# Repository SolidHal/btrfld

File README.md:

# btrfld and btrfld_ulp

Pronounced "butter-fold"

A foldable, portable sibling of the btrfly keyboard https://github.com/SolidHal/btrfly-keyboard

and a variant, the btrfld ulp (ultra low profile)

More images available in "FinishedPictures" folder

the btrfld folding and unfolding

the btrfld ultra low profile (ulp) from above

the handwired and pcb version of the choc btrfld

the btrfld ultra low profile (ulp) from above, folded

the handwired and pcb version of the choc btrfld, folded up

the btrfld ultra low profile (ulp) next to the btrfld pcb aka choc (its 7mm thinner!)

the handwired and pcb version of the choc btrfld with its sibling, the btrfly

## Features
- 5 key dactyl-manuform-mini thumb cluster
- flat, tented qwerty keys
- 6 extra mappable keys
- bluetooth (optional)
- folds flat for portability

- btrfld
  - choc switches
  - ~22.5 mm thick
  
- btrfld ulp
  - cherry mx ulp switches
  - ~15.5 mm thick

- 15.5mm thick (btrfld ulp)
- 22.5mm thick (btrfld)

## PCBs

- located in `btrfld_pcb`
- the hand and thumb pcbs are mirrored so they can be used for either hand
- 2 x btrfld_pcb
- 1 x btrfld_pcb_center
- 2 x btrfld_pcb_thumb

## Parts:

- PCBs

- USB C breakout basic breakout board
  - Used this one https://www.amazon.com/Type-C-Breakout-Serial-Connector-Converter/dp/B09KC1SMGD/
  - wiring the usb:
  ```
  For most usages, you can just connect VBUS to your 5V input, GND to ground, and D+ and D- as you expect. You can monitor the CC and SBU pins to determine cable polarity, or send side-band data. Or leave them disconnected
  ```

- A USB 2.0 USB C cable to cut up
  - USB C to Micro usb can be gotten pretty cheap

- 46 choc v1 keyswitches, keycaps OR 46 Cherry MX ULP switches
  - https://github.com/pashutk/Cherry_MX_ULP has information on finding ulp switches
  - if you choose to use ULP switches, you will need to order the solder paste stencils as well as the pcbs and get a hotplate so you can solder them
  - There aren't amazing sources of ULP key caps at this point. The best option i found was to print some. The stls can be found in `ulp_keycap` and `ulp_keycap_homenub` directories. You need a reasonably high resolution SLA printer to get functional keycaps, FDM won't work. 

- 1N4148W SOD-323F diodes
  - Tips for soldering these can be found in the assembly notes section below

- 3mm diameter steel rod
  - 2x 70.5mm
  - 2x 64.7mm
  - 2x 22.7 mm
  - 4x 14.2

- 1.27mm flat ribbon cable
  - 2 x 9 wire cables: 13 cm
  - 2 x 6 wire cables: 9.6 cm

- 1x nicenano OR bluemicro840
  - if you don't want bluetooth, you can just use a promicro instead

- 3d printed pieces, located in the STLs folder
  - 1 copy of everything besides test_fit-UnderbodyWireGuides.stl, which we need 4 of

## Print Settings:
```
Supports on buildplate
Detect Bridging
100% infill
0.20mm
PLA/PETG
```

## Assembly Tips
this process is much less tedious than hand wiring. But its still annoying in places since we are trying to keep things thin.

- btrfld (non-ulp)
    - solder the parallel wires to the hands/thumb clusters *before* placing the boards in the frame and soldering switches
    - trim the stabs on the hinge side keys of the left/right hand bodies (switches for Q,A,Z, P, ;, / keys)

- btrfld ulp
    - use your hotplate to solder the switches first, then the diodes, then the parallel wires. you can then install the pcbs into the 3d printed frames
    - you might need to use something to support balance some switches while solder, since some are only partially supported by the PCB
    - the tolerance between the keycaps and the frames is quite tight. do some testing (and likely sanding) before fully assembling to ensure nothing sticks
    
- stripping ribbon cable:
  - take an xacto knife ~3mm from the end of the cable and cut a slit until you see wire, then use your fingernail to peel the cut off section away from the rest of the cable
- use cut off diode/resistor legs to connect the controller to the center pcb
- the pcbs are designed to hold the diodes "upside down" to keep things as thin as possible. Soldering these is a little hard since they like to stick to the soldering iron.
  - get some fine point electronics tweezers
  - put a very very small amount of solder on one of the diode pads
  - place the diode, the "legs" should keep the diode from completely falling into the hole
  - hold the diode down with the tweezers, and use your iron to reflow the solder. This should hold the diode down enough for you to solder the other diode leg.
  - finally, add some more solder to the first pad
- The UnderbodyWireGuides get super glued into the holes of the pcb. See pictures of the hand underside for details.
- Once you have tested the board, use some superglue to reinforce the ribbon cable solder joints

- Reference the images in the "BuildPictures/PCB" folder

## Flash ZMK Firmware

Prebuilt firmware available in the `Firmware` directory
Bridge ground + reset twice quickly to put the bluemicro840 into flashing mode
Or press the "bootloader" key on the keyboard if you have already flashed the firmware before
then copy the firmware onto the keyboard
```
cp build/zephyr/zmk.uf2 /media/<user>/NRF52BOOT/CURRENT.UF2
```

## Build ZMK Firmware

### Github Actions Build

_This is broken until https://github.com/zmkfirmware/zmk/pull/1499 merges, do a local build instead_
fork this repo, modify the files to your hearts content
the github actions workflow will then build it for you
https://github.com/SolidHal/zmk-config-btrfld

### Local build

Grab my fork of the zmk firmware
```
git clone https://github.com/SolidHal/zmk.git
```

follow https://zmk.dev/docs/development/setup
then
```
cd zmk
cd app
west build -b bluemicro840_v1 -- -DSHIELD=btrfld
```

make pristine
```
west build -p -b bluemicro840_v1 -- -DSHIELD=btrfld
```

## Future development
- Attach trackpoint/ball or touchpad somewhere?
- latch to keep folded?
- latches to retain body/thumb extensions in base?

## Modifying
Edit `test_fit.FCStd` using FreeCad, I used version `0.19-24366`
I am by no means a FreeCad expert, so I'm sure it is built suboptimally.
The pcbs were created in kicad

## Hand Wiring Assembly Tips

### Don't hand wire this thing unless you have lots and lots of time to waste. Use the PCBs instead.

- Wiring the underside of the right/left body halves is very tedious
  - Make sure everything stays as flat as possible

- Reference the images in "BuildPictures" and "FinishedPictures" for hints on how to layout the wires

- Reference WiringGuide.png to see see the row/colomn layout

- Must trim a very very slight amount off of the center pin on keyswitches over the body/thumbcluster rod
  - switch above this must be rotated to give clearance for the rod locker

- Body/ThumbCluster Pivot Rob
  - BodyThumbRod Cap gets glued on body end of rod
  - thumb cluster end of rod gets glued in place

- Area around the body/baseplate hinge needs clearence, so keep all wires to the other side of the keyswitch

- Reference the images in the "BuildPictures" folder

### Hand Wiring Wire lengths:

#### Body -> Baseplate
9 wires
420mm

#### Thumb -> Baseplate
6 wires
240mm
70mm threaded through on the thumb side

## References

Animation:
BaseBodyAngle goes from 0 -> 32

firmware:
https://zmk.dev/docs/development/new-shield
https://zmk.dev/docs/development/setup/
https://zmk.dev/docs/troubleshooting
https://github.com/SolidHal/zmk

Friction fit redesign notes:
https://markforged.com/resources/blog/joinery-onyx
https://www.hubs.com/knowledge-base/how-design-snap-fit-joints-3d-printing/

Cherry MX ULP references:
https://github.com/pashutk/Cherry_MX_ULP

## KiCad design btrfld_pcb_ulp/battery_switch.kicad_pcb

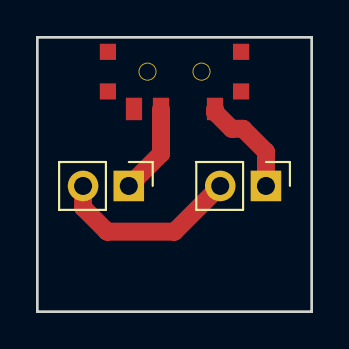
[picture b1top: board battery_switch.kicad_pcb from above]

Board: 2 copper layers, 15.2 x 15.2 mm, 3 parts (0 on the bottom side), 3 nets.

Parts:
J1, J2: Conn_01x02; Pin_Header_Straight_1x02_Pitch2.54mm
SW1: SW_SPDT; SPDT_C128955

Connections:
unnamed: J1.1, SW1.2
unnamed: J1.2, J2.2
unnamed: J2.1, SW1.1

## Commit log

2021-12-21 initial test fit files
2021-12-21 add thumb portion to fit test
2021-12-24 change thumb cluster angle to 40 deg
2021-12-24 add stl, sliced files
2021-12-27 bodies with pivot points
2021-12-30 begin assembly
2021-12-30 aligned LCSes
2021-12-30 map out baseplate
2021-12-31 adjusted pivots to fix 3mm rods
2021-12-31 correct baseplace length
2022-01-01 add readme with partslist
2022-01-01 adjust hole size, baseplate size from 2nd draft print
2022-01-01 add demo animation
2022-01-01 fix demo video, seems freecad outputs weirdness
2022-01-01 need to figure out thumb baseplate attachement
2022-01-01 try smaller support for thumbs
2022-01-01 make thumb right its own piece
    it needs to be unique from thumb left
2022-01-04 cleanup thumb sketch
    - begin work on thumb extension
2022-01-04 rough shape of thumb extension figured out
2022-01-04 get better idea of the thumb extension
2022-01-04 magnetic connector checkpoint
    making the extension wide enough to fit the magnetic connector
    requires either
    1) putting a hole in the baseplate
    2) making the space between the baseplate and the bode/thumb larger
    (2) is bad because we don't want to increase the thickness of the entire
    keyboard
2022-01-05 mapped out one side of extension slot
2022-01-05 bottom, top sketch of baseplate hole for thumb extension
2022-01-06 setup right extension
    cleanup repo
2022-01-06 baseplate thumb extension holes slightly larger
    added route for baseplate body support hinge
2022-01-07 increase thumb extension gap
2022-01-07 support placed
2022-01-07 reduce clearance on thumb extension pivot
2022-01-07 checkpoint
2022-01-07 create sketchs for top and bottom of extension slot
2022-01-07 finally got the subtractive loft to work
2022-01-08 after a bunch of trig, top of slight is aligned
2022-01-08 make body/baseplate hinge 1.7r
2022-01-08 make long holes teardrop shaped
2022-01-09 make baseplate body support hinge larger
2022-01-09 correct baseplate body angle
2022-01-09 add print time reducer for body
2022-01-09 lengthen thumb extension
2022-01-09 add thumb extension stopper
2022-01-09 reworking baseplate/body support, checkpoint
2022-01-11 add symmetric body/baseplate support
2022-01-11 completed baseplate body support
2022-01-11 correct body support spacing
2022-01-11 move supports in a bit to make slicer happy
2022-01-12 remove external references on body pieces
2022-01-12 move thumb clusters inward
2022-01-12 adjust thumb cluster angle
2022-01-13 clean up attactment points
2022-01-13 move thumb cluter hinge up
2022-01-13 Revert "move thumb cluter hinge up"
    This reverts commit d1044715d7c4dff2feddb821aab7251de043a833.
2022-01-13 fixup thumb extension baseplate slots
2022-01-13 change angle of thumb cluster to body
2022-01-13 fixup thumb extension and thumb placement to fit angle change
2022-01-13 correct thumb cluster body linear extension
2022-01-13 correct thumb extension baseplate slots
2022-01-13 make the quick print cutout better
2022-01-14 move thumb cluster closer
2022-01-15 move thumb cluster even closer
2022-01-15 correct thumb angle, correct extension slots
2022-01-20 trim baseplate height, tighten thumb hinges
2022-01-20 add magnet holes
2022-02-25 add wiring guide base image
2022-03-17 add full wiring guide
2022-03-17 fill out TODO
2022-03-26 create baseplate wiring cavity
    - picked out controller location
    - add STLs
2022-03-29 map out wire routing
2022-03-29 add bodythumbcluster rod cap
2022-03-29 add body/thumb rod caps to assembly
2022-03-29 added wire routing to body, choc retaining clip slots to body
2022-03-29 add pocket to body baseplate support for choc key pins
2022-03-29 revert thumb extension shrink
2022-03-29 added thumb extension wire guide, adjusted baseplate cavity
2022-03-30 adjust choc clip slots, wiring guides on thumb
2022-03-30 add thumb cluster wire management to baseplate
2022-03-30 added wire management to body
    increased wire slots from 1mm -> 2mm
2022-03-30 added 1.2mm chamfer to body, thumb
2022-03-30 shrink body thumb rod cap to 1.6mm
2022-03-31 adjst body cable management
2022-03-31 add usb breakout board cutout, adjust baseplate wire management
2022-04-01 add controller cutout to baseplate
2022-04-01 chamfer baseplate
2022-04-01 increase body wire manager slot side
2022-04-05 update readme with some build tips
2022-04-07 add firmware notes
2022-04-27 Add images, demo gif
2022-04-27 cleanup README, add firmware
2022-04-27 add more wiring info
2022-04-27 add steel rod lengths
2022-04-27 add images of it folded
2022-05-19 small changes
2022-05-19 thumb cluster pockets
2022-05-19 more readme
2022-05-24 more changes
2022-06-06 body mostly done, some changes to baseplate
2022-06-13 baseplate complete
2022-06-13 wirepockets done
2022-06-14 body and baseplate done, some changes to assembly
2022-06-15 correct thumb support size
2022-06-15 start new support cutout
2022-06-15 ok thumb support cut
2022-06-15 main support cutout
2022-06-15 think its done
2022-06-15 missing pocket
2022-06-15 first export
2022-06-16 updated wire pocket for another wire
2022-11-12 add updated firmware
2023-01-26 created left/right hand pcb
2023-01-27 add pcb for center board
2023-01-27 correct column 5 trace on center pcb
    add center pcb to cad
2023-01-27 created thumb pcb
2023-01-27 move old stls to HANDWIRE_STLS
2023-01-31 add pcb compatible stls
2023-02-07 fixup spacing around thumb cluster pcb
2023-02-07 fixup flipped diode holes so copper connects pads on either side of board
    also fixup some tracing while we are at it
2023-02-22 add firmware with led support
2023-02-22 add UnderbodyWireGuides
2023-02-22 add pcb build pictures, update README
2023-02-22 add folding animation of pcb version
2023-02-22 use looping folding animation
2023-02-22 try again
2023-02-24 update firmware
2023-02-24 add license
2024-08-14 add cherry mx ulp pcb, begin work on cad
2024-08-16 rename cad ulp files
2024-08-16 add keycap cad
2024-08-16 export pcb as step file
2024-08-16 before widening key holes in btrfld cad ulp
2024-08-16 widened key holes, need to fix right hand
2024-08-16 made keyswitch holes larger to fit the ulp switches
2024-08-16 install ulp thumb pcb into cad
2024-08-16 made ulp thumb keyswitch holes bigger
2024-08-28 add pcb restraint holes to hand cad
2024-09-04 place and test body pcb and cad screw holes
2024-09-04 added faster holes to pcb & cad thumb, reviewed traces
2024-09-04 remove pads & holes that fall of the edge of the board
2024-09-04 pcbs reviewed
2024-09-16 thined out the ulp baseplate
2024-09-16 fix sharp edges on thumb/body
2024-09-17 correct keycap home nub location
2024-09-27 finialize btrfld ulp cad and stls
2024-09-27 update documentation to include btrfld ulp
2024-09-27 update thickness comparison subtitle
2025-02-19 add newer firmware
2025-02-19 add stencil for the btrfld ulp baseplate
